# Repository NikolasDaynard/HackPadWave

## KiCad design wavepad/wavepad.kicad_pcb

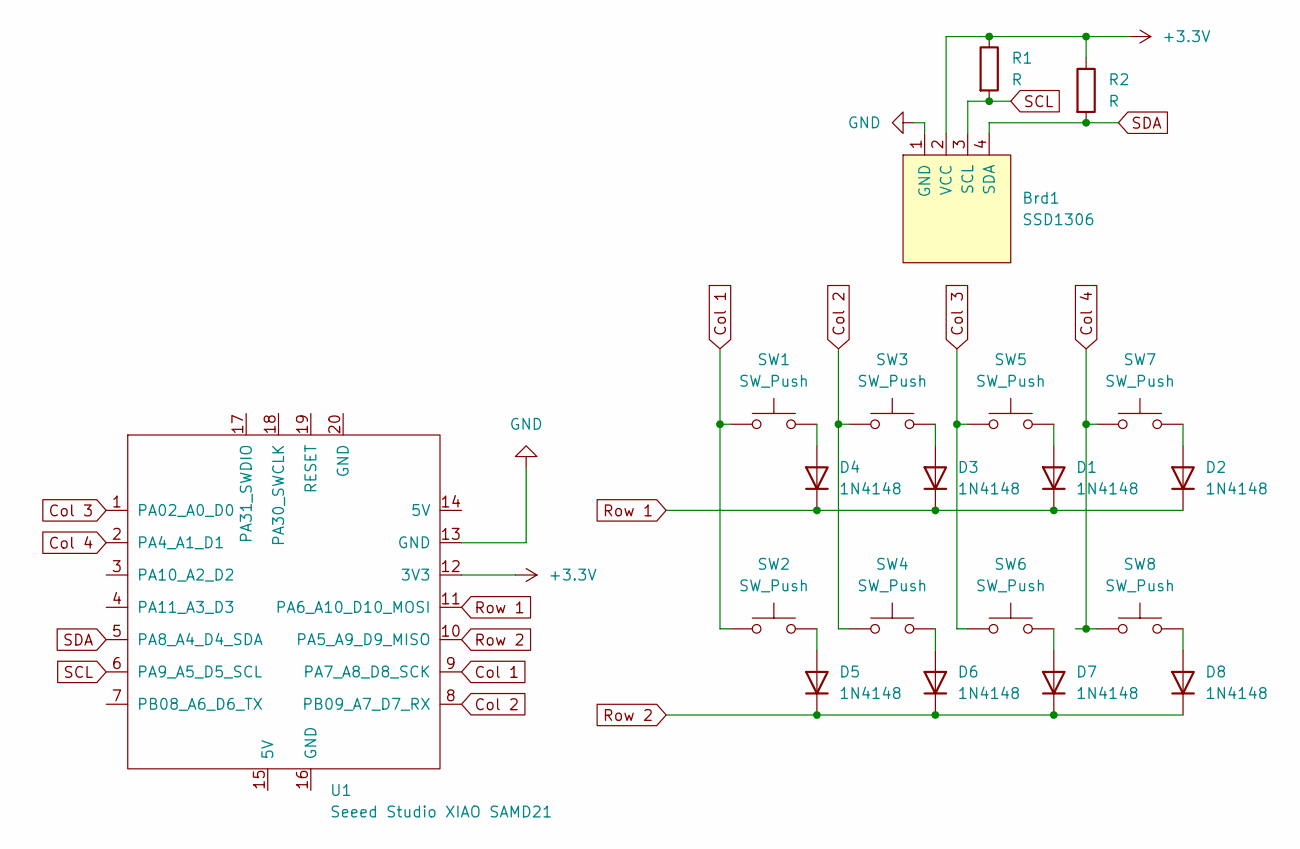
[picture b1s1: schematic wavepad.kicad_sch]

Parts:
Brd1: SSD1306; SSD1306-0.91-OLED-4pin-128x32
D1, D2, D3, D4, D5, D6, D7, D8: 1N4148; D_DO-35_SOD27_P7.62mm_Horizontal
R1, R2: R; R_Axial_DIN0309_L9.0mm_D3.2mm_P15.24mm_Horizontal
SW1, SW2, SW3, SW4, SW5, SW6, SW7, SW8: SW_Push; SW_Cherry_MX_1.00u_PCB
U1: Seeed Studio XIAO SAMD21; XIAO-SAMD21-RP2040-14P-2.54-21X17.8MM (Seeeduino XIAO)

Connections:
+3.3V: Brd1.2 (VCC), R1.1, R2.1, U1.12 (3V3)
Col 1: SW1.1, SW2.1, U1.9 (PA7_A8_D8_SCK)
Col 2: SW3.1, SW4.1, U1.8 (PB09_A7_D7_RX)
Col 3: SW5.1, SW6.1, U1.1 (PA02_A0_D0)
Col 4: SW7.1, SW8.1, U1.2 (PA4_A1_D1)
GND: Brd1.1 (GND), U1.13 (GND)
unnamed: D1.2 (A), SW5.2
unnamed: D2.2 (A), SW7.2
unnamed: D3.2 (A), SW3.2
unnamed: D4.2 (A), SW1.2
unnamed: D5.2 (A), SW2.2
unnamed: D6.2 (A), SW4.2
unnamed: D7.2 (A), SW6.2
unnamed: D8.2 (A), SW8.2
Row 1: D1.1 (K), D2.1 (K), D3.1 (K), D4.1 (K), U1.11 (PA6_A10_D10_MOSI)
Row 2: D5.1 (K), D6.1 (K), D7.1 (K), D8.1 (K), U1.10 (PA5_A9_D9_MISO)
SCL: Brd1.3 (SCL), R1.2, U1.6 (PA9_A5_D5_SCL)
SDA: Brd1.4 (SDA), R2.2, U1.5 (PA8_A4_D4_SDA)

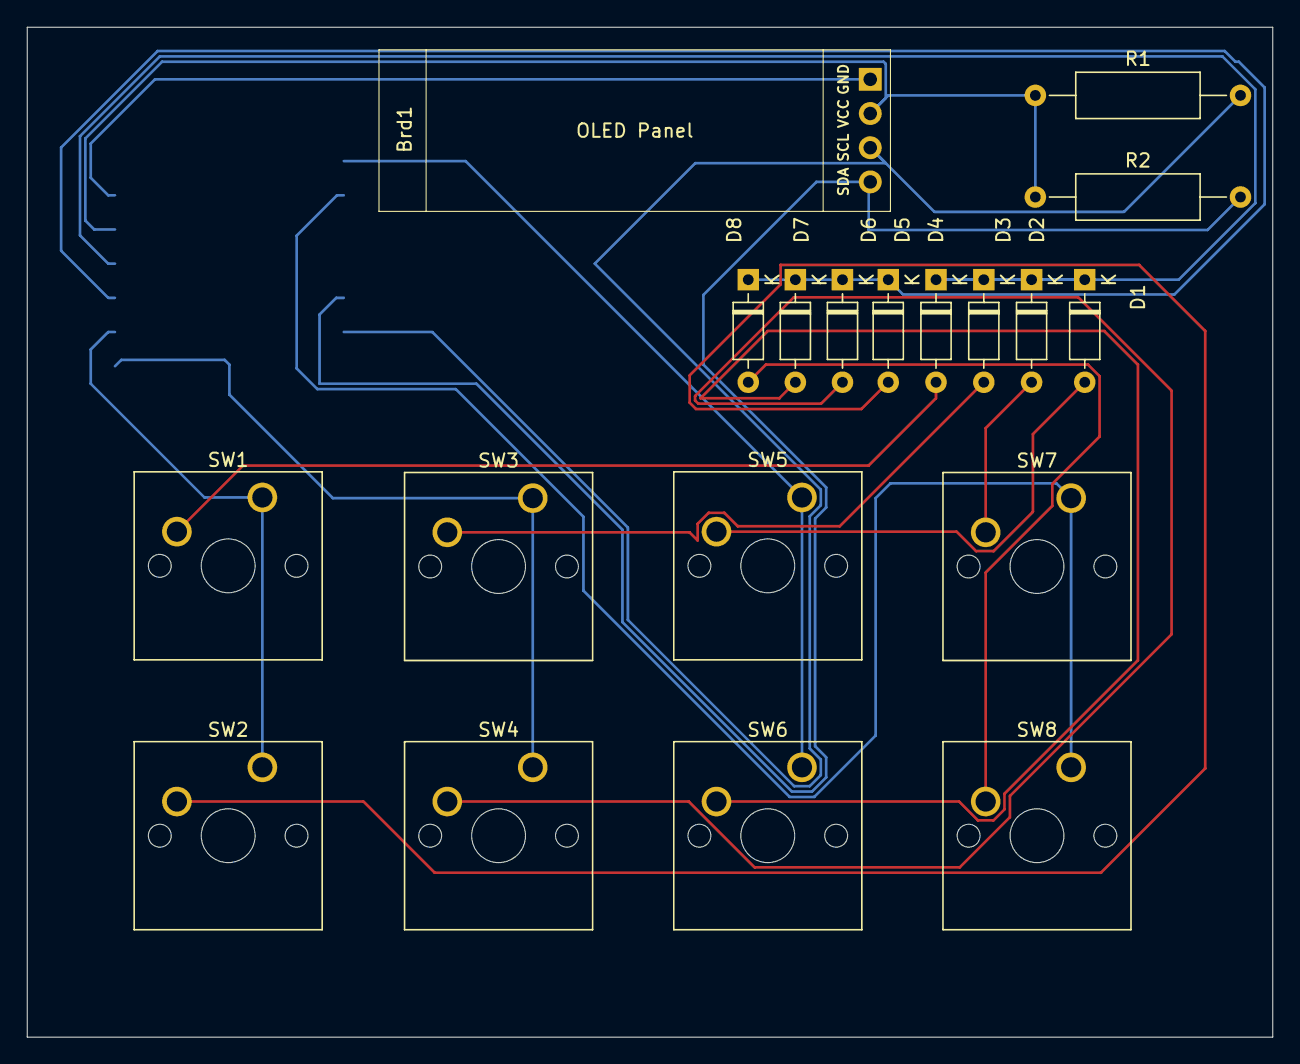
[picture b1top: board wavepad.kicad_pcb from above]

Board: 2 copper layers, 92.5 x 75.0 mm, 20 parts (1 on the bottom side), 18 nets.

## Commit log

2024-10-02 init
2024-10-02 testing
2024-10-02 last ver
2024-10-05 actually finish design
2024-10-05 add resistors to oled
